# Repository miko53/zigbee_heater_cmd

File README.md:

# zigbee_heater_cmd
PIC SW to programm electrical heater by zigbee.

this sw is a firmware for PIC micro in order to command by zigbee a electrical heater.

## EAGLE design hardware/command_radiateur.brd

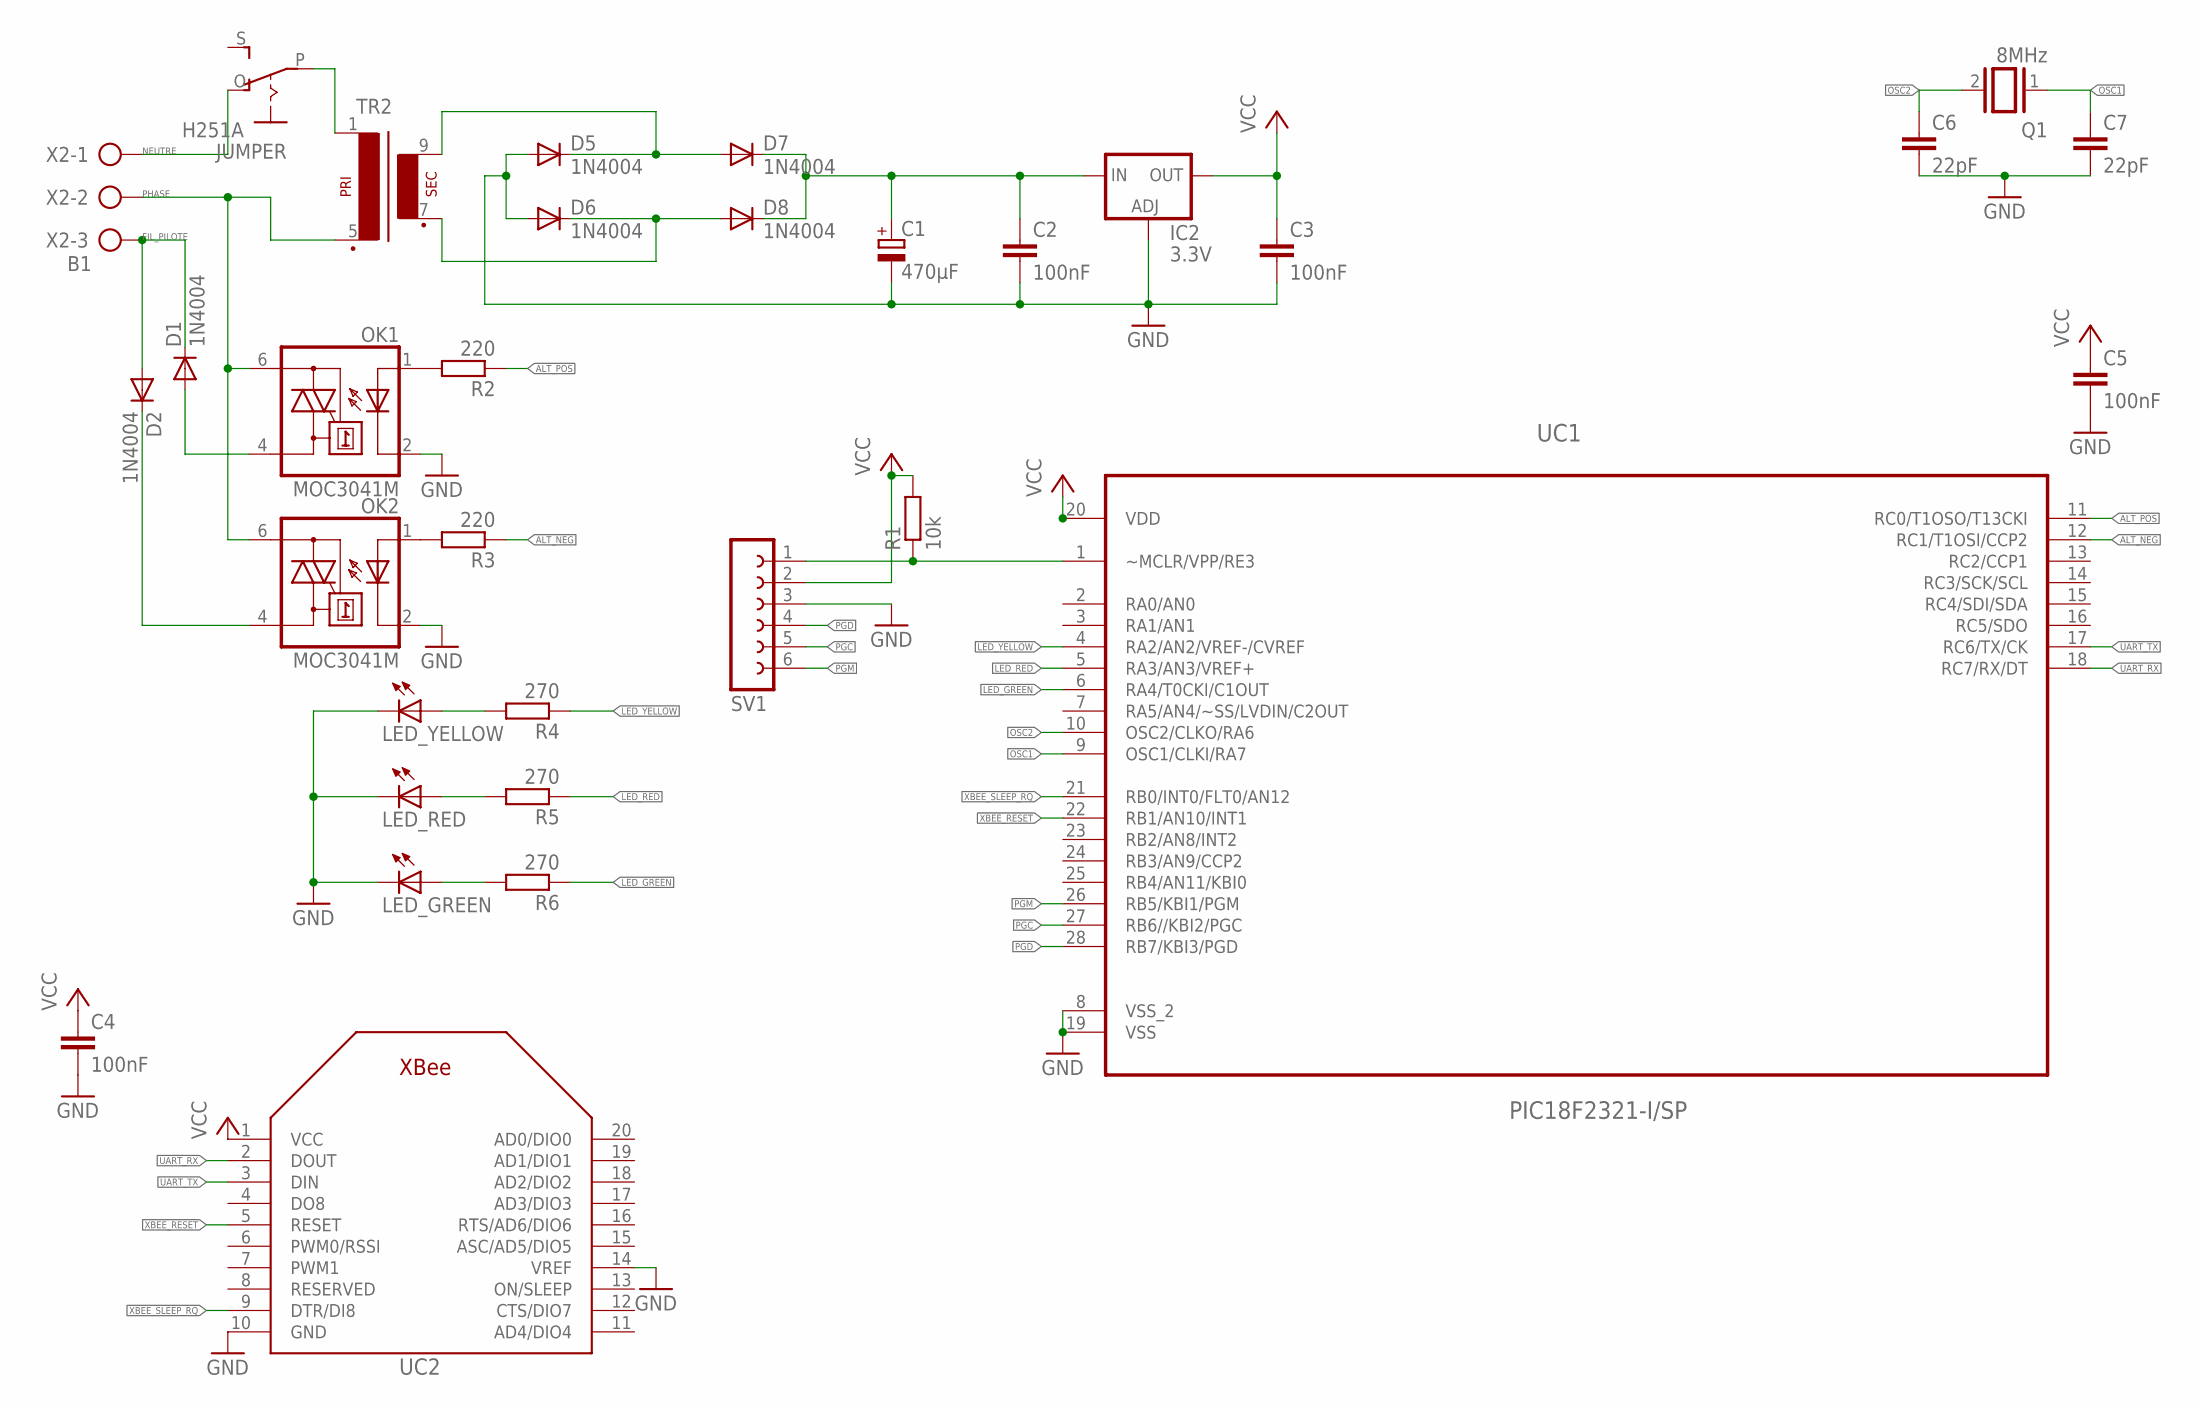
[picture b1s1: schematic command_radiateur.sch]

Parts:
C1: 470µF; E5-10,5
C2, C3, C4, C5: 100nF; C050-030X075
C6, C7: 22pF; C025-024X044
D1, D2, D5, D6, D7, D8: 1N4004; DO41-10
IC2: 3.3V; 317TS
JUMPER: H251A
LED_GREEN: LED3MM
LED_RED: LED3MM
LED_YELLOW: LED3MM
OK1, OK2: MOC3041M; DIL06
Q1: 8MHz; QS
R1: 10k; 0204/7
R2, R3: 220; 0204/7
R4, R5, R6: 270; 0204/7
SV1: FE06-1; FE06
TR2: VV11
UC1: PIC18F2321-I/SP; DIP254P762X508-28
UC2: XBEE
X2: B1; AK300/3

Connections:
ALT_NEG: R3.1, UC1.12 (RC1/T1OSI/CCP2)
ALT_POS: R2.1, UC1.11 (RC0/T1OSO/T13CKI)
FIL_PILOTE: D1.C, D2.A, X2.3
GND: C1.-, C2.2, C3.2, C4.2, C5.2, C6.2, C7.2, D5.A, D6.A, IC2.1 (ADJ), LED_GREEN.K (C), LED_RED.K (C), LED_YELLOW.K (C), OK1.2 (C), OK2.2 (C), SV1.3, UC1.8 (VSS_2), UC1.19 (VSS), UC2.10 (GND), UC2.14 (VREF)
LED_GREEN: R6.1, UC1.6 (RA4/T0CKI/C1OUT)
LED_RED: R5.1, UC1.5 (RA3/AN3/VREF+)
LED_YELLOW: R4.1, UC1.4 (RA2/AN2/VREF-/CVREF)
N1: JUMPER.P, TR2.1
unnamed: R1.1, SV1.1, UC1.1 (~MCLR/VPP/RE3)
unnamed: OK1.1 (A), R2.2
unnamed: OK2.1 (A), R3.2
unnamed: D1.A, OK1.4 (A1)
unnamed: D5.C, D7.A, TR2.9 (S4)
unnamed: D6.C, D8.A, TR2.7 (S3)
unnamed: C1.+, C2.1, D7.C, D8.C, IC2.3 (IN)
unnamed: D2.C, OK2.4 (A1)
unnamed: LED_YELLOW.A, R4.2
unnamed: LED_RED.A, R5.2
unnamed: LED_GREEN.A, R6.2
NEUTRE: JUMPER.O, X2.1
OSC1: C7.1, Q1.1, UC1.9 (OSC1/CLKI/RA7)
OSC2: C6.1, Q1.2, UC1.10 (OSC2/CLKO/RA6)
PGC: SV1.5, UC1.27 (RB6//KBI2/PGC)
PGD: SV1.4, UC1.28 (RB7/KBI3/PGD)
PGM: SV1.6, UC1.26 (RB5/KBI1/PGM)
PHASE: OK1.6 (A2), OK2.6 (A2), TR2.5 (P2), X2.2
UART_RX: UC1.18 (RC7/RX/DT), UC2.2 (DOUT)
UART_TX: UC1.17 (RC6/TX/CK), UC2.3 (DIN)
VCC: C3.1, C4.1, C5.1, IC2.2 (OUT), R1.2, SV1.2, UC1.20 (VDD), UC2.1 (VCC)
XBEE_RESET: UC1.22 (RB1/AN10/INT1), UC2.5 (RESET)
XBEE_SLEEP_RQ: UC1.21 (RB0/INT0/FLT0/AN12), UC2.9 (DTR/DI8)

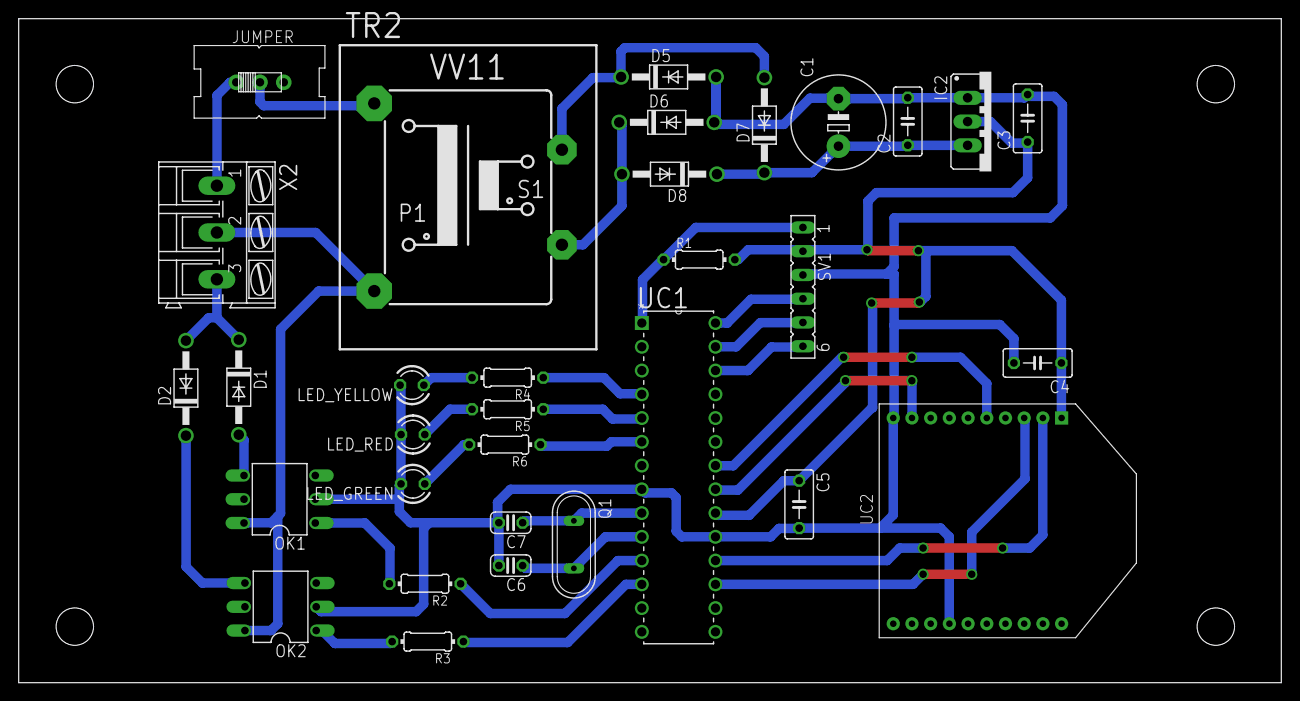
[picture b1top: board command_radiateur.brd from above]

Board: 2 copper layers, 135.0 x 71.0 mm, 32 parts (0 on the bottom side), 31 nets.

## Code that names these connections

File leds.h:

/*
 * File:   leds.h
 * Author: mickael
 *
 * Created on 10 décembre 2017, 17:02
 */

#ifndef LEDS_H
#define	LEDS_H

#include <xc.h>
#include <stdint.h>

#ifdef	__cplusplus
extern "C" {
#endif

#define     LED_YELLOW      (0x01)
#define     LED_RED         (0x02)
#define     LED_GREEN       (0x04)


#define     leds_set(leds)   LATD |= leds;
#define     leds_reset(leds) LATD &= ~(leds);

extern void leds_glitch(uint8_t leds);


#ifdef	__cplusplus
}
#endif

#endif	/* LEDS_H */

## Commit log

2018-01-01 first version which receives order and send reply in controller
2018-01-02 add heater command, no more by leds
2018-01-02 add confort minus 1 and confort minus 2 command
2018-01-02 management of CONFORT-1 and CONFORD-2 and send of status each 90s
2018-03-10 OSC in High Speed mode (8MHz)
2018-03-10 move src code in firmware folder, add license
2018-03-10 adaptation of software to hardware based on PIC18LF2420
2018-03-10 add schematics
2018-03-25 update PCB size, insert hole to insert into G368 box
2018-10-15 after trial with received board - it seems that a spurious framing error occurs and reset processor sometimes at boot. This part has been removed and work properly
2018-11-03 minor beautiful modification + remove unused dbg functions
